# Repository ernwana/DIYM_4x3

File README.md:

4x3 Macropad with Dual Rotary Encoders:

This repository contains the firmware, PCB design files, and documentation for a custom-built 4x3 macropad featuring two rotary encoders, powered by an RP2040 Zero microcontroller and programmed using the QMK (Quantum Mechanical Keyboard) firmware.

Features:

4x3 Key Matrix: 12 customizable mechanical keys arranged in a 4x3 layout.
2 Rotary Encoders: Can be used for volume control, scrolling, or any other action supported by QMK.
RP2040 Zero: Small, powerful microcontroller ideal for custom keyboard projects.
Customizable Firmware: Programmed with QMK firmware, offering extensive customization for key functions, encoder actions, layers, and more.
Open Source Hardware and Firmware: All design files and firmware are open-source.

Project Overview:

This macropad is designed to enhance productivity and streamline workflows for creative professionals, developers, and gamers. The device provides 12 keys, which can be programmed with single keystrokes, macros, or shortcuts, and two rotary encoders that can handle tasks such as volume adjustment or scrolling.

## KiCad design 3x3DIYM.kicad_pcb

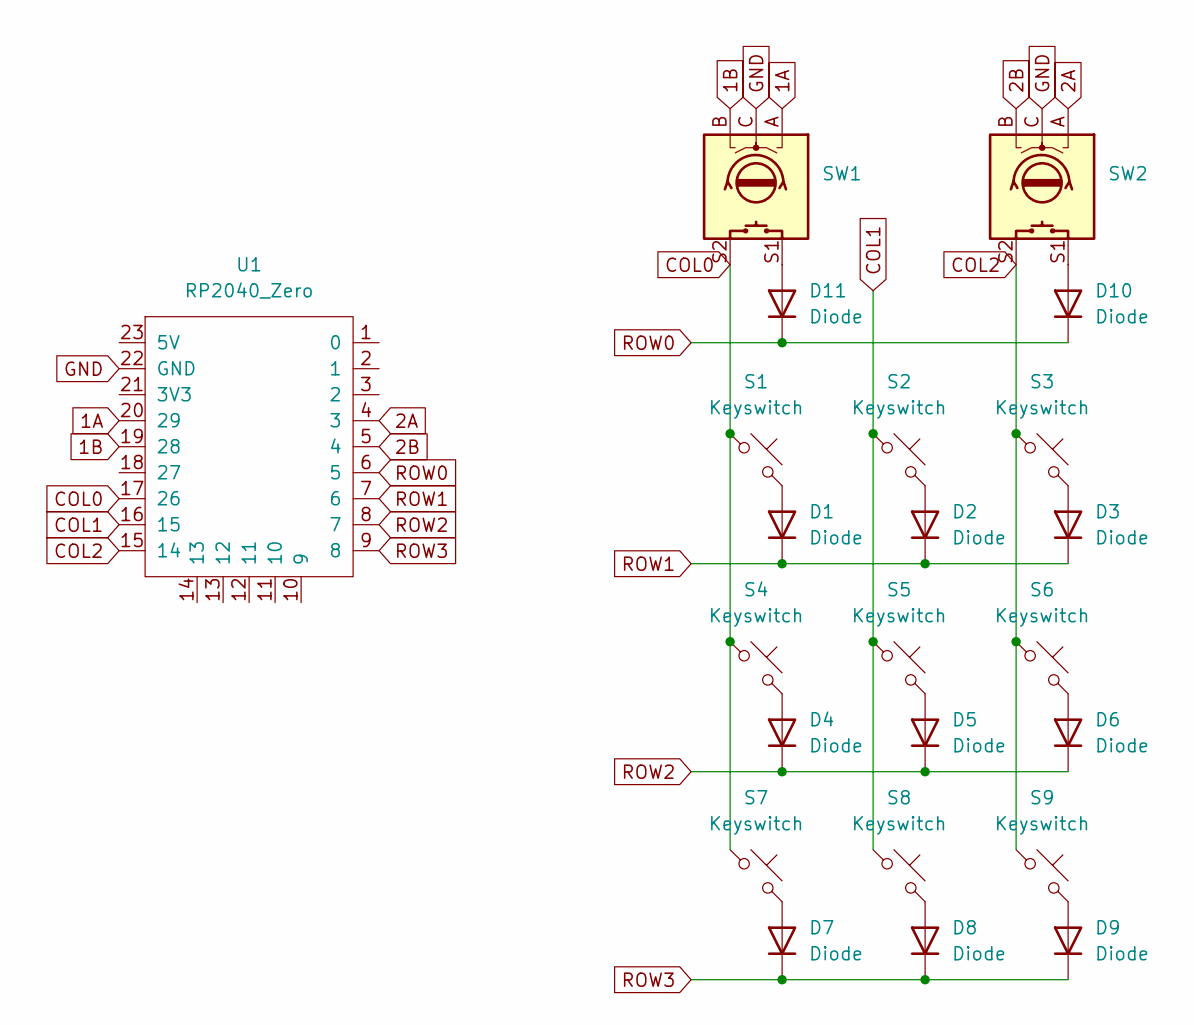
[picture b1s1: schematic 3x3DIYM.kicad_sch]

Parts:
D1, D2, D3, D4, D5, D6, D7, D8, D9, D10, D11: Diode; Diode_SOD-123
S1, S2, S3, S4, S5, S6, S7, S8, S9: Keyswitch; Hotswap_MX_1.00u
SW1, SW2: RotaryEncoder_Switch; RotaryEncoder_Alps_EC11E-Switch_Vertical_H20mm
U1: RP2040_Zero

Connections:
1A: SW1.A, U1.20 (29)
1B: SW1.B, U1.19 (28)
2A: SW2.A, U1.4 (3)
2B: SW2.B, U1.5 (4)
COL0: S1.1, S4.1, S7.1, SW1.S2, U1.17 (26)
COL1: S2.1, S5.1, S8.1, U1.16 (15)
COL2: S3.1, S6.1, S9.1, SW2.S2, U1.15 (14)
GND: SW1.C, SW2.C, U1.22 (GND)
unnamed: D1.2 (A), S1.2
unnamed: D2.2 (A), S2.2
unnamed: D3.2 (A), S3.2
unnamed: D4.2 (A), S4.2
unnamed: D5.2 (A), S5.2
unnamed: D6.2 (A), S6.2
unnamed: D7.2 (A), S7.2
unnamed: D8.2 (A), S8.2
unnamed: D9.2 (A), S9.2
unnamed: D10.2 (A), SW2.S1
unnamed: D11.2 (A), SW1.S1
ROW0: D10.1 (K), D11.1 (K), U1.6 (5)
ROW1: D1.1 (K), D2.1 (K), D3.1 (K), U1.7 (6)
ROW2: D4.1 (K), D5.1 (K), D6.1 (K), U1.8 (7)
ROW3: D7.1 (K), D8.1 (K), D9.1 (K), U1.9 (8)

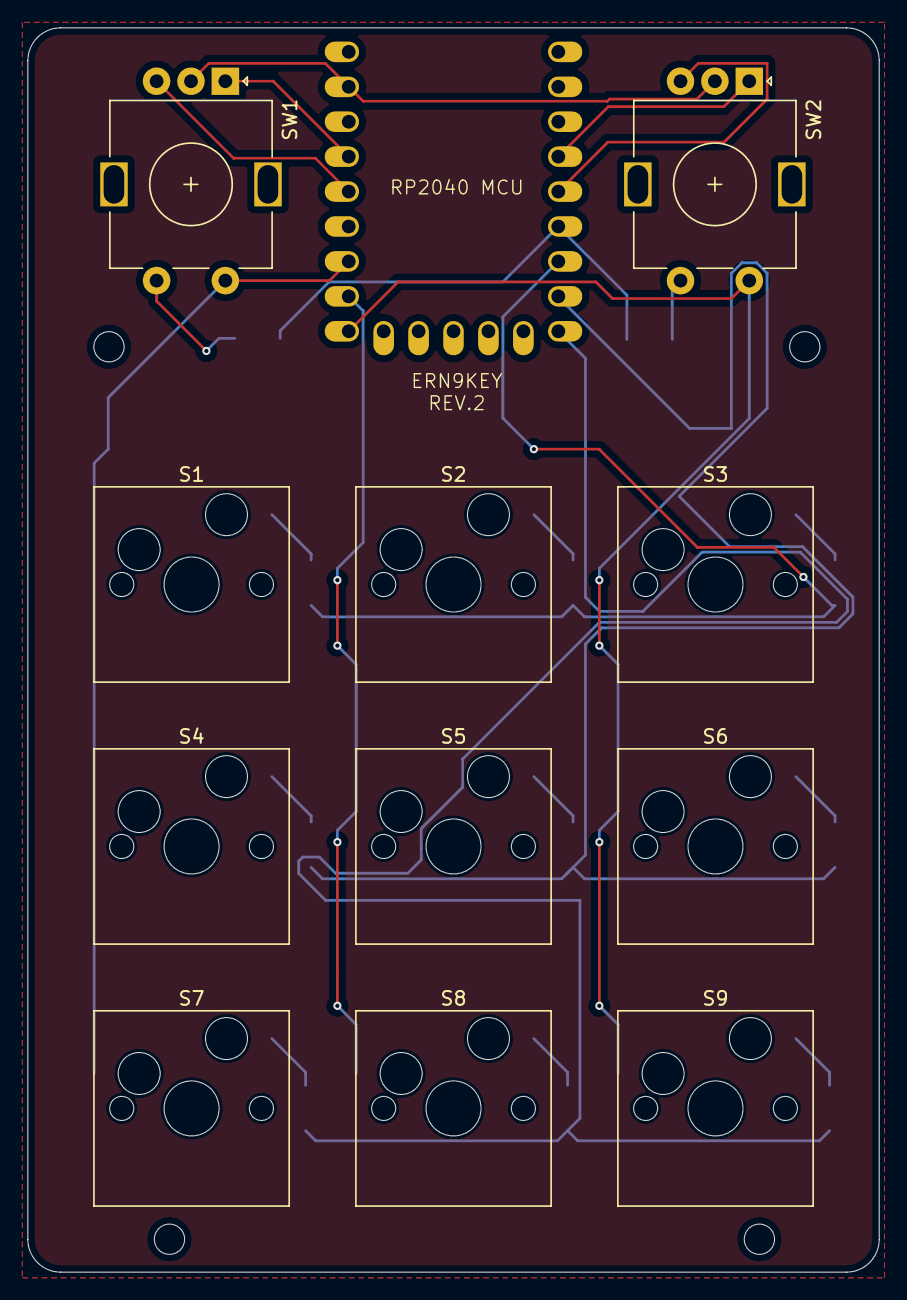
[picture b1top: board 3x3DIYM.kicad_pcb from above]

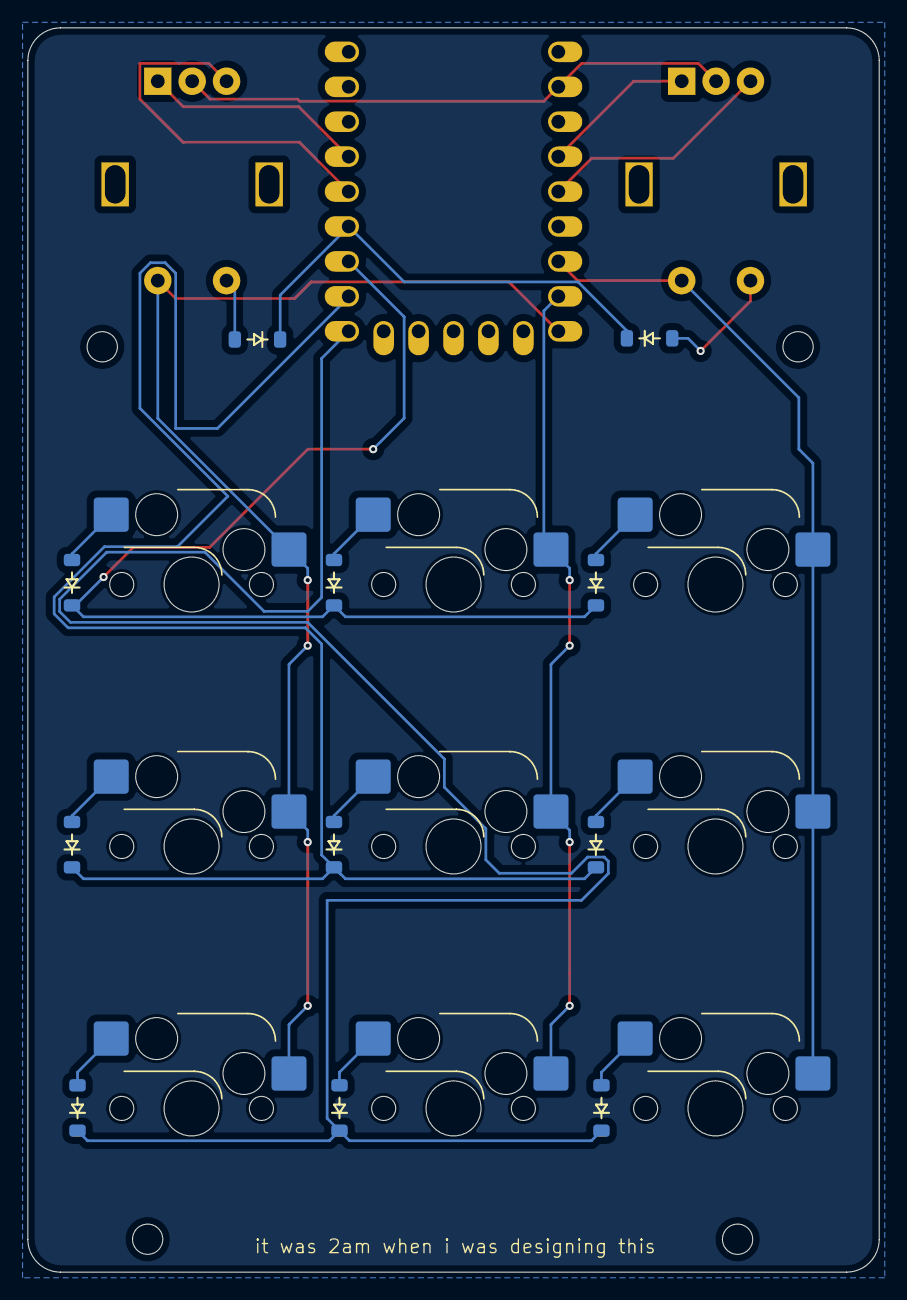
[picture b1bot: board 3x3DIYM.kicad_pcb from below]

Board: 2 copper layers, 61.9 x 90.5 mm, 23 parts (11 on the bottom side), 23 nets.
